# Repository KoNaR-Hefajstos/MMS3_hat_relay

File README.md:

# MMS3 Hat Relay

## Sekcja 1: Dokumentacja Hat'a

### Krótki opis projektu
Hat realizuje funkcję 5-kanałowego sterownika przekaźników. Umożliwia przełączanie prądu o max parametrach 230V AC / 5A na kanał.

### Zgodność ze standardem ChainBus

* ✅ Używa złącza ChainBus, nie zmienia jego miejsca ani pinoutu.
* ✅ Używa wyłącznie interfejsu I2C do komunikacji zewnętrznej (działa w trybie Slave, nie inicjuje transmisji jako Master).
* ✅ Spełnia wymagania mechaniczne standardu (wymiary PCB, rozstaw otworów).
* ❌ Pobiera maksymalny prąd zgodny z ilością na jednego hat'a:  Jeden aktywny przekaźnik pobiera ok. 80 mA z linii 5V. Przy załączeniu wszystkich 5 kanałów jednocześnie hat pobiera **400 mA**, a max to 125mA.
* ✅ Obsługuje napięcie wejściowe BRD_VIN do wartości 48V.

### Komunikacja i adresowanie

#### Adresacja I2C
Komunikacja z modułem odbywa się za pomocą magistrali I2C.

| Układ (IC)   | Funkcja                                  |       Adres I2C (7-bit)        |
| :----------- | :--------------------------------------- | :----------------------------: |
| **CH32V003** | Mikrokontroler (programowalny ekspander) | *Definiowany w oprogramowaniu* |
| **M24C64-W** | Pamięć Identyfikajcji EEPROM             |             `0x50`             |

### Pinout mikrokontrolera CH32V003
Połączenia wewnętrzne sygnałów sterujących przekaźnikami oraz magistrali I2C:

| Pin MCU | Rola / Nazwa sygnału | Opis funkcjonalny                                      |
| :------ | :------------------- | :----------------------------------------------------- |
| **PC1** | I2C SDA              | Linia danych magistrali I2C (podłączona do ChainBus)   |
| **PC2** | I2C SCL              | Linia zegarowa magistrali I2C (podłączona do ChainBus) |
| **PC7** | K1                   | Sterowanie przekaźnikiem 1 (CN1)                       |
| **PC3** | K2                   | Sterowanie przekaźnikiem 2 (CN2)                       |
| **PC4** | K3                   | Sterowanie przekaźnikiem 3 (CN3)                       |
| **PC5** | K4                   | Sterowanie przekaźnikiem 4 (CN4)                       |
| **PC6** | K5                   | Sterowanie przekaźnikiem 5 (CN5)                       |

### Pinout złączy wykonawczych

Moduł wyposażony jest w 5 złączy oznaczonych jako CN1 do CN5 podłączonych do przekaźników.

| Złącze    | Opis pinu               | Funkcja                                                                                                                    |
| :-------- | :---------------------- | :------------------------------------------------------------------------------------------------------------------------- |
| **CN1-5** | Pin 1<br>Pin 2<br>Pin 3 | **NO** (Normally Open - normalnie otwarty)<br>**COM** (Common - wspólny)<br>**NC** (Normally Closed - normalnie zamknięty) |

### Szczegółowy opis techniczny
Hat z 5 kanałami przekaźników 5A 230VAC. Przekaźniki sa galwanicznie izolowane od MCU oraz każdy kanał ma diode LED do oznaczania swojej aktywacji.

Sygnały sterowane są z mikrokontrolera CH32V003 który robi za expander GPIO po I2C.

Każdy przekaźnik pobiera po ~80mA, więc właczenie wszystkich na raz przekracza limit prądu 1 hat'a

### Gotowe arkusze hierarchiczne
W projekcie wydzielono następujące moduły schematyczne:
* **CH32v003** – Arkusz zawierający strukturę mikrokontrolera, oscylator, przycisk reset, złącze programowania SWD (w standardzie WCH-Link).

* **Przekaźnik z optoizolacją** – Schemat pojedynczego kanału przekaźnika zawierający optoizolator, tranzystor 3V3 -> 5V, diodę zabezpieczającą, diodę LED sygnalizującą stan pracy oraz złącze wyjściowe.

---

## Sekcja 2: Specyfikacja standardu ChainBus

### Architektura i łączenie modułów
Standard ChainBus umożliwia modułowe łączenie hatów. Na jednym MMS3 można zamontować pionowo **do 8 hat'ów**. Połączenie realizowane jest poprzez wpięcie złącza męskiego kolejnego hat'a w złącze żeńskie poprzedniego.

### Komunikacja i sterowanie
Magistrala ChainBus jest w pełni cyfrowa. Płyta główna nie steruje bezpośrednio sygnałami ogólnego przeznaczenia (GPIO) na poszczególnych hat'ach. Wszelkie operacje (np. obsługa diod LED, odczyt krańcówek, sterowanie przekaźnikami) muszą być realizowane przez dedykowane układy scalone (np. ekspandery portów, mikrokontrolery pomocnicze) komunikujące się przez interfejsy systemowe.

Wybór aktywnego modułu realizowany jest przez układ przełącznika magistrali (bus switch) na płycie głównej. Dzięki temu linie I2C, SPI i UART są niezależne dla każdego hat'a (brak konfliktów adresów I2C między różnymi hatami).
* **Identyfikacja:** Każdy moduł powinien posiadać pamięć EEPROM na magistrali I2C w celu identyfikacji płyty przez system - układ M24C64-W skonfigurowany na adres `0x50` przy liniach adresowych A0, A1, A2 zwartych do masy.

### Zasilanie
Złącze ChainBus dostarcza następujące linie zasilania:

| Magistrala zasilania | Napięcie znamionowe | Maksymalny prąd (łączny dla 8 hatów) | Szacowany prąd na jeden hat |
| :------------------- | :-----------------: | :----------------------------------: | :-------------------------: |
| **5V**               |        5.0 V        |                1.0 A                 |           125 mA            |
| **12V stby**         |       12.0 V        |                0.5 A                 |            65 mA            |
| **BRD_VIN**          |   12.0 V – 48.0 V   |                1.5 A                 |           185 mA            |

*   Komponenty podłączone do linii `BRD_VIN` muszą być przystosowane do pracy z napięciem od 12V do **48 V**.

### Wymagania mechaniczne i złącza
* **Wymiary PCB:** Niedozwolona jest zmiana obrysu płytki oraz położenia otworów montażowych, aby zachować kompatybilność mechaniczną.
* **Pozycjonowanie złączy ChainBus:** Położenie złącza standardu 2x16 SMD (raster 2.54 mm) musi być zgodne z szablonem. Złącze żeńskie montowane jest na stronie FRONT, natomiast złącze męskie na stronie BACK.
* **Interfejsy zewnętrzne:** Złącza wejścia/wyjścia oraz ewentualne wysokonapięciowe wyjścia przekaźnikowe powinny być umieszczone przy dolnej krawędzi płytki, z zachowaniem odpowiednich odstępów izolacyjnych (clearance/creepage) wymaganych przy napięciu 230V.
* **Komponenty:** Wszystkie komponenty powinny znajdować się na stronie FRONT płytki, aby uniknąć kolizji mechanicznych z elementami sąsiadujących modułów w stosie.

---

## Sekcja 3: Licencje

### Licencje projektu

*   **PCB:** CERN-OHL-P
*   **Software:** MIT License

[Template](https://github.com/KoNaR-Hefajstos/MMS3_hat_templates/) jest na licencji CC0 1.0 Universal. **Reszta projektu nie jest na tej licencji**

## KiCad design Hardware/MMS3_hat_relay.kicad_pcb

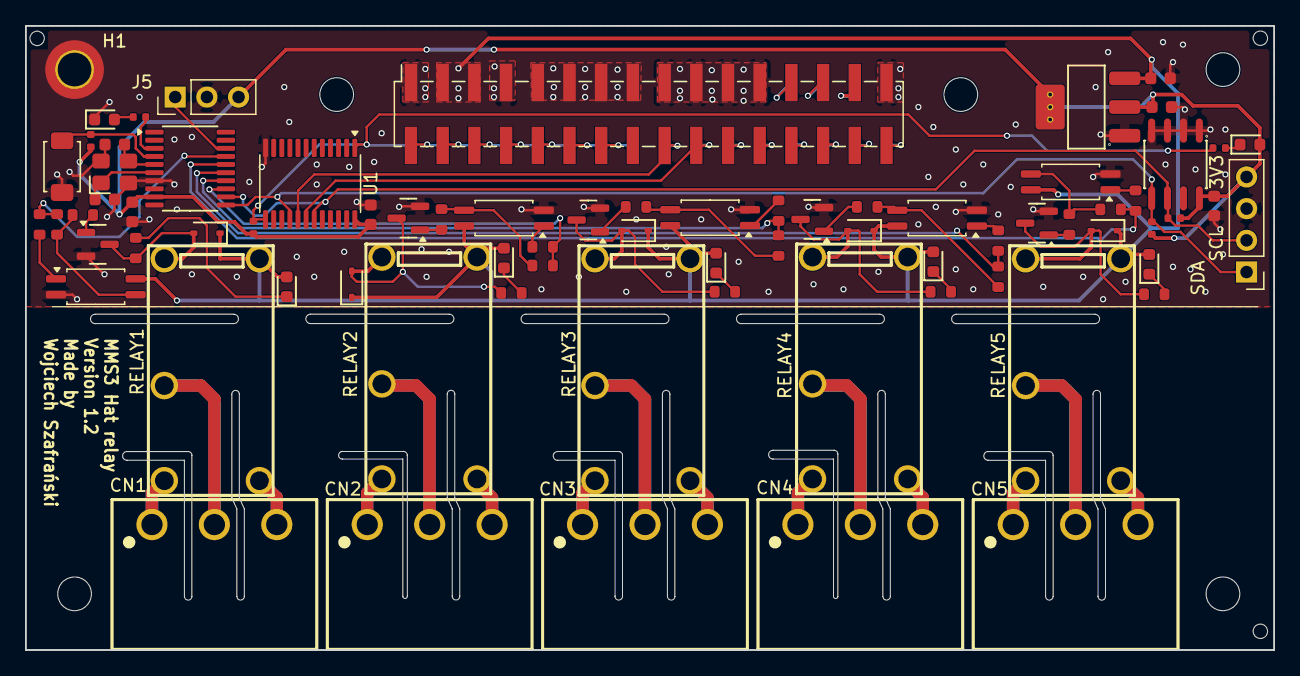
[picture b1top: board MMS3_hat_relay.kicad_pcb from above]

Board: 2 copper layers, 100.0 x 50.0 mm, 84 parts (1 on the bottom side), 77 nets.

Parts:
C1, C2, C3: 100nF; C_0603
C4, C5: 12pF; C_0603
C16, C18: 10uF; C_0603
CN1, CN2, CN3, CN4, CN5: DB2ERC-5.0-3P-GN; CONN-TH_3P-P5.00_DB2ERC-5.0-3P-GN
D1, D3, D9, D10, D11, D12, D13: Red; D_0603
D2, D4, D5, D6, D8: 1N5819WS; D_SOD-323
H1: M2.5 Mount; MountingHole_2.7mm_M2.5_DIN965_Pad_TopOnly
H2, H3, H4, H5, H6: M2.5 mount; MountingHole_2.7mm_M2.5
H7, H8, H9: Hole_Tooling_JLCPCB
J1: Chainbus in; PinHeader_2x16_P2.54mm_Vertical_SMD
J2: Chainbus Out; PinSocket_2x16_P2.54mm_Vertical_SMD
J3: Conn_01x04_Pin; PinHeader_1x04_P2.54mm_Vertical
J5: Program; PinHeader_1x03_P2.54mm_Vertical
Q12, Q13, Q14, Q15, Q16: MMBT5551 200-300; Q_SOT-23
R1, R14: 330Ω; R_0402
R4, R6, R10, R13: 10kΩ; R_0402
R15, R19, R22, R25, R28: 0Ω; R_0603
R16, R20, R23, R26, R29: 2kΩ; R_0603
R17, R18, R21, R24, R27: 100Ω; R_0603
R30, R31, R32, R33, R34: 1kΩ; R_0603
RELAY1, RELAY2, RELAY3, RELAY4, RELAY5: JE-105D_C3250129; RELAY-TH_JE-1XXD
S1: Tactile Button, 160gf; SW_TS-1088-AR02016
U1: SN74CB3Q3384APW; TSSOP-24_4.4x7.8mm_P0.65mm
U2: M24C64; SOIC-8_L5.0-W4.0-P1.27-LS6.0-BL
U3: CH32V003FxPx; TSSOP-20_4.4x6.5mm_P0.65mm
U4: AMS1117; SOT-223-3_L6.5-W3.4-P2.30-LS7.0-BR
U5, U6, U7, U8, U9: LTV-217-B-G; SOP-4_4.4x2.6mm_P1.27mm
X1: X322525MOB4SI; OSC-SMD_4P-L3.2-W2.5-BL

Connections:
+3V3: C1.1, C2.1, C3.1, C18.1, D3.2, J3.4, J5.3, R4.2, R6.1, R10.1, R13.1, U1.24 (VCC), U2.8 (VCC), U3.9 (VDD), U4.2 (VOUT), U4.4 (VOUT)
+5V: C16.1, D2.1, D4.1, D5.1, D6.1, D8.1, D9.2, D10.2, D11.2, D12.2, D13.2, J1.3, J1.5, J2.3, J2.5, RELAY1.5, RELAY2.5, RELAY3.5, RELAY4.5, RELAY5.5, U4.3 (VIN), U5.4, U6.4, U7.4, U8.4, U9.4
+12V stby: J1.29, J2.29
/Bus_switch/Chainbus_In.SCL: J1.20, J2.20, U1.18 (2A3)
/Bus_switch/Chainbus_In.SDA: J1.18, J2.18, U1.17 (2A2)
/Bus_switch/SEL1: J1.2, R1.1, R4.1, U1.1 (~1OE), U1.13 (~2OE)
/CH32V003/CH32V003.RX: R14.1, U3.3 (PD6)
/CH32V003/OSCI: C4.1, U3.5 (PA1), X1.3 (OSC)
/CH32V003/OSCO: C5.1, U3.6 (PA2), X1.1 (OSC)
/CH32V003/PD7: R13.2, S1.1 (A), U3.4 (PD7)
/CH32V003/SWIO: J5.1, U3.18 (PD1)
/Chainbus.SCL: J3.2, R6.2, U1.19 (2B3), U2.6 (SCL), U3.12 (PC2)
/Chainbus.SDA: J3.1, R10.2, U1.16 (2B2), U2.5 (SDA), U3.11 (PC1)
/Interboard_connector/Chainbus.CS: J1.22, J2.22
/Interboard_connector/Chainbus.MISO: J1.28, J2.28
/Interboard_connector/Chainbus.MOSI: J1.26, J2.26
/Interboard_connector/Chainbus.RX: J1.32, J2.32
/Interboard_connector/Chainbus.SCK: J1.24, J2.24
/Interboard_connector/Chainbus.TX: J1.30, J2.30
/Interboard_connector/R1: J1.25, J2.25
/Interboard_connector/R2: J1.27, J2.27
/Interboard_connector/SEL2: J1.4, J2.2
/Interboard_connector/SEL3: J1.6, J2.4
/Interboard_connector/SEL4: J1.8, J2.6
/Interboard_connector/SEL5: J1.10, J2.8
/Interboard_connector/SEL6: J1.12, J2.10
/Interboard_connector/SEL7: J1.14, J2.12
/Interboard_connector/SEL8: J1.16, J2.14
/Relay 1/COM: CN1.2, RELAY1.2
/Relay 1/NC: CN1.3, RELAY1.4
/Relay 1/NO: CN1.1, RELAY1.3
/Relay 2/COM: CN2.2, RELAY2.2
/Relay 2/NC: CN2.3, RELAY2.4
/Relay 2/NO: CN2.1, RELAY2.3
/Relay 3/COM: CN3.2, RELAY3.2
/Relay 3/NC: CN3.3, RELAY3.4
/Relay 3/NO: CN3.1, RELAY3.3
/Relay 4/COM: CN4.2, RELAY4.2
/Relay 4/NC: CN4.3, RELAY4.4
/Relay 4/NO: CN4.1, RELAY4.3
/Relay 5/COM: CN5.2, RELAY5.2
/Relay 5/NC: CN5.3, RELAY5.4
/Relay 5/NO: CN5.1, RELAY5.3
/S1: R15.1, R17.1, U3.17 (PC7)
/S2: R18.1, R19.1, U3.13 (PC3)
/S3: R21.1, R22.1, U3.14 (PC4)
/S4: R24.1, R25.1, U3.15 (PC5)
/S5: R27.1, R28.1, U3.16 (PC6)
GND: C1.2, C2.2, C3.2, C4.2, C5.2, C16.2, C18.2, D1.1, H1.1 (1_1), J1.1, J1.7, J1.17, J1.19, J1.21, J1.23, J1.31, J2.1, J2.7, J2.17, J2.19, J2.21, J2.23, J2.31, J3.3, J5.2, Q12.2 (E), Q13.2 (E), Q14.2 (E), Q15.2 (E), Q16.2 (E), S1.2 (B), U1.12 (GND), U2.1 (A0), U2.2 (A1), U2.3 (A2), U2.4 (VSS), U3.7 (VSS), U4.1 (GND), U5.2, U6.2, U7.2, U8.2, U9.2, X1.2 (GND), X1.4 (GND)
unnamed: D1.2, R14.2
unnamed: D3.1, R1.2
unnamed: D9.1, R30.2
unnamed: D10.1, R31.2
unnamed: D11.1, R32.2
unnamed: D12.1, R33.2
unnamed: D13.1, R34.2
unnamed: Q12.1 (B), R16.2
unnamed: D2.2, Q12.3 (C), R30.1, RELAY1.1
unnamed: Q13.1 (B), R20.2
unnamed: D4.2, Q13.3 (C), R31.1, RELAY2.1
unnamed: Q14.1 (B), R23.2
unnamed: D5.2, Q14.3 (C), R32.1, RELAY3.1
unnamed: Q15.1 (B), R26.2
unnamed: D6.2, Q15.3 (C), R33.1, RELAY4.1
unnamed: Q16.1 (B), R29.2
unnamed: D8.2, Q16.3 (C), R34.1, RELAY5.1
unnamed: R15.2, R16.1, U5.3
unnamed: R17.2, U5.1
unnamed: R18.2, U6.1
unnamed: R19.2, R20.1, U6.3
unnamed: R21.2, U7.1
unnamed: R22.2, R23.1, U7.3
unnamed: R24.2, U8.1
unnamed: R25.2, R26.1, U8.3
unnamed: R27.2, U9.1
unnamed: R28.2, R29.1, U9.3
VIN_CHAINBUS: J1.9, J1.11, J1.13, J1.15, J2.9, J2.11, J2.13, J2.15

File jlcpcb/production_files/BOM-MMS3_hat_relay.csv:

Comment,Designator,Footprint,LCSC,Quantity
100nF,"C1,C2,C3",C_0603,C14663,3
100Ω,"R17,R18,R21,R24,R27",R_0603,C22775,5
10kΩ,"R10,R13,R4,R6",R_0402,C25744,4
10uF,"C16,C18",C_0603,C19702,2
12pF,"C4,C5",C_0603,C38523,2
1N5819WS,"D2,D4,D5,D6,D8",D_SOD-323,C191023,5
1kΩ,"R30,R31,R32,R33,R34",R_0603,C21190,5
2kΩ,"R16,R20,R23,R26,R29",R_0603,C22975,5
330Ω,"R1,R14",R_0402,C25104,2
AMS1117,U4,SOT-223-3_L6.5-W3.4-P2.30-LS7.0-BR,C6186,1
DB2ERC-5.0-3P-GN,"CN1,CN2,CN3,CN4,CN5",CONN-TH_3P-P5.00_DB2ERC-5.0-3P-GN,C5445289,5
JE-105D_C3250129,"RELAY1,RELAY2,RELAY3,RELAY4,RELAY5",RELAY-TH_JE-1XXD,C3250129,5
LTV-217-B-G,"U5,U6,U7,U8,U9",SOP-4_4.4x2.6mm_P1.27mm,C115450,5
M24C64,U2,SOIC-8_L5.0-W4.0-P1.27-LS6.0-BL,C79988,1
MMBT5551 200-300,"Q12,Q13,Q14,Q15,Q16",Q_SOT-23,C2145,5
Red,"D1,D10,D11,D12,D13,D3,D9",D_0603,C2286,7
SN74CB3Q3384APW,U1,TSSOP-24_4.4x7.8mm_P0.65mm,C469874,1
"Tactile Button, 160gf",S1,SW_TS-1088-AR02016,C720477,1
X322525MOB4SI,X1,OSC-SMD_4P-L3.2-W2.5-BL,C9006,1
CH32V003FxPx,U3,TSSOP-20_4.4x6.5mm_P0.65mm,,1
Chainbus Out,J2,PinSocket_2x16_P2.54mm_Vertical_SMD,,1
~,H8,Hole_Tooling_JLCPCB,,1
Conn_01x04_Pin,J3,PinHeader_1x04_P2.54mm_Vertical,,1
~,H7,Hole_Tooling_JLCPCB,,1
~,H9,Hole_Tooling_JLCPCB,,1
Program,J5,PinHeader_1x03_P2.54mm_Vertical,,1
Chainbus in,J1,PinHeader_2x16_P2.54mm_Vertical_SMD,,1

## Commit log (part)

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2026-05-12 done
2026-05-13 fixed NPN configuration in optocoupler
2026-05-15 changed headers and relays to better one
2026-06-08 BREAKING: updated CH32v003 programming pinout
2026-06-09 added documentation
2026-06-09 added licenses
